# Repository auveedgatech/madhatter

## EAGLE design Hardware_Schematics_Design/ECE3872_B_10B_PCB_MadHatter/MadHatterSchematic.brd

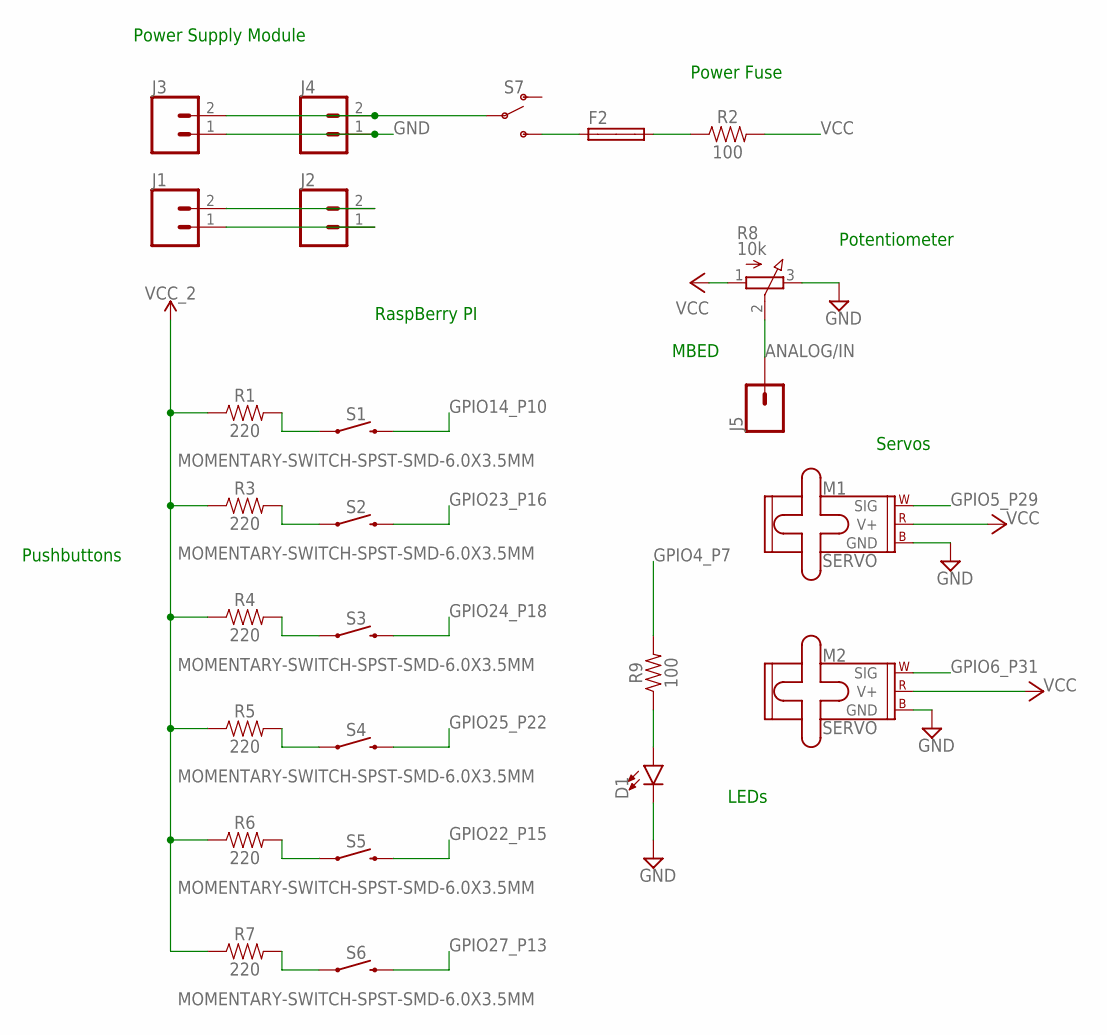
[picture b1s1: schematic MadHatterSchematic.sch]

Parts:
D1: LED0603; LED-0603
F2: SHKOG
J1, J2, J3, J4: CONN_02PTH_RA_FEMALE; 1X02_RA_PTH_FEMALE
J5: CONN_01SNAP-FEMALE; SNAP-FEMALE
M1, M2: SERVO; 1X03
R1, R3, R4, R5, R6, R7: 220; 0402-TIGHT
R2, R9: 100; 0402-TIGHT
R8: 10k; 3RP/1610N
S1, S2, S3, S4, S5, S6: MOMENTARY-SWITCH-SPST-SMD-6.0X3.5MM; TACTILE_SWITCH_SMD_6.0X3.5MM
S7: SWITCH-SPDT-PTH-11.6X4.0MM; SWITCH_SPDT_PTH_11.6X4.0MM

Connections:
ANALOG/IN: J5.1, R8.2 (S)
GND: D1.C, J1.1, J2.1, J3.1, J4.1, M1.3 (GND), M2.3 (GND), R8.3 (E)
GPIO4_P7: R9.2
GPIO5_P29: M1.1 (SIG)
GPIO6_P31: M2.1 (SIG)
GPIO14_P10: S1.2
GPIO22_P15: S5.2
GPIO23_P16: S2.2
GPIO24_P18: S3.2
GPIO25_P22: S4.2
GPIO27_P13: S6.2
unnamed: F2.1A, S7.3 (S)
unnamed: R3.2, S2.1
unnamed: F2.2A, R2.1
unnamed: D1.A, R9.1
unnamed: R1.2, S1.1
unnamed: R4.2, S3.1
unnamed: R5.2, S4.1
unnamed: R6.2, S5.1
unnamed: R7.2, S6.1
VCC: J1.2, J2.2, J3.2, J4.2, M1.2 (V+), M2.2 (V+), R2.2, R8.1 (A), S7.2
VCC_2: R1.1, R3.1, R4.1, R5.1, R6.1, R7.1

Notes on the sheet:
Power Supply Module
Potentiometer
Servos
LEDs
Pushbuttons
Power Fuse
MBED
RaspBerry PI

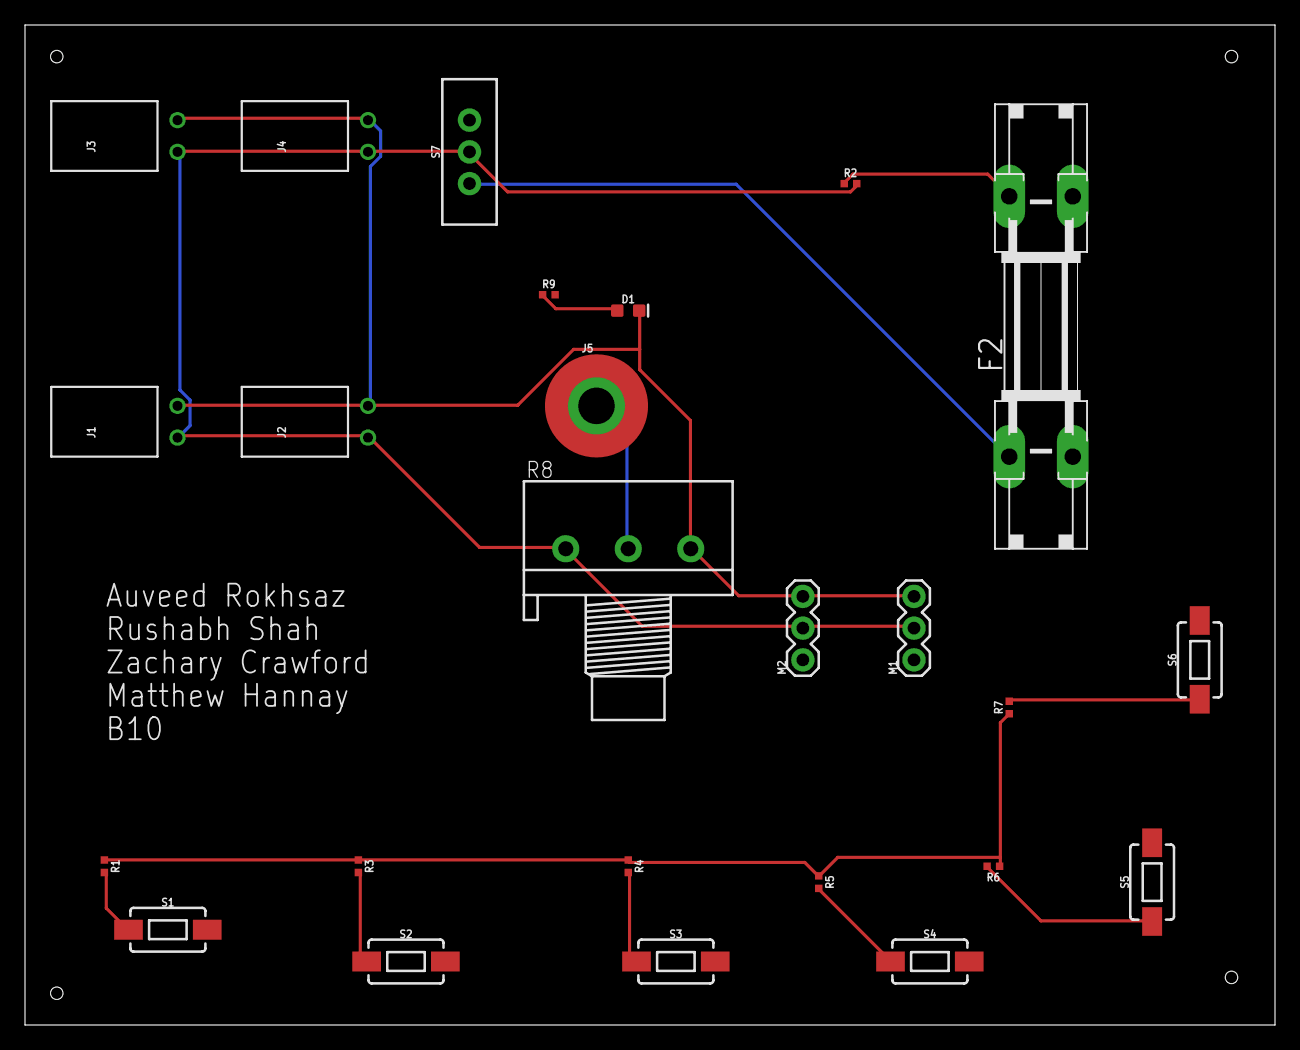
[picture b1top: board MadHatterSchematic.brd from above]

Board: 2 copper layers, 100.0 x 80.0 mm, 25 parts (0 on the bottom side), 13 nets.

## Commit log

2022-10-13 Sandbox Code
2022-10-13 State Machine Start
2022-10-14 State Machine
2022-10-14 Director Code
2022-10-14 Eagle Files Added
2022-10-14 Keys added
2022-10-14 CPP code
2022-11-01 volume
2022-11-01 Volume control 1
2022-11-01 Larger state control
2022-11-01 Restructure
2022-11-02 Hatter
2022-11-07 token
2022-11-08 MadHatterwav

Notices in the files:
parts and their libraries:
SparkFun-LED: Licensing: Creative Commons ShareAlike 4.0 International - https://creativecommons.org/licenses/by-sa/4.0
